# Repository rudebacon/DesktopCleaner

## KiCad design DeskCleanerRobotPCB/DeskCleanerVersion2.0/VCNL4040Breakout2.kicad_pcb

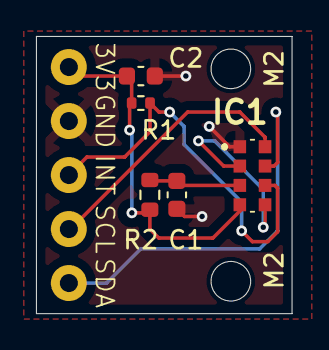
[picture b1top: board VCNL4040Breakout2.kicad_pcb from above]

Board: 2 copper layers, 14.2 x 15.4 mm, 12 parts (0 on the bottom side), 7 nets.

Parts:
3V3: +3.3V; Soldering_Holes_1mmH_2mmPad
C1: 0.1uF; C_0603_1608Metric
C2: 2.2uF; C_0603_1608Metric
GND: GND; Soldering_Holes_1mmH_2mmPad
IC1: VCNL4040M3OE
INT: INT1; Soldering_Holes_1mmH_2mmPad
M2, M2#2: MountingHole_2.2mm_M2
R1: 8.2k; R_0402_1005Metric
R2: 22; R_0603_1608Metric
SCL: SCL; Soldering_Holes_1mmH_2mmPad
SDA: SDA; Soldering_Holes_1mmH_2mmPad

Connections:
GND: C1.2, C2.2, GND.1, IC1.1 (GND)
unnamed: 3V3.1, C2.1, IC1.4 (A), R1.1, R2.2
unnamed: IC1.6 (INT), INT.1, R1.2
unnamed: IC1.2 (K(SENSOR)), IC1.5 (K(LED))
unnamed: IC1.8 (SCLK), SCL.1
unnamed: IC1.7 (SDAT), SDA.1
unnamed: C1.1, IC1.3 (VDD), R2.1

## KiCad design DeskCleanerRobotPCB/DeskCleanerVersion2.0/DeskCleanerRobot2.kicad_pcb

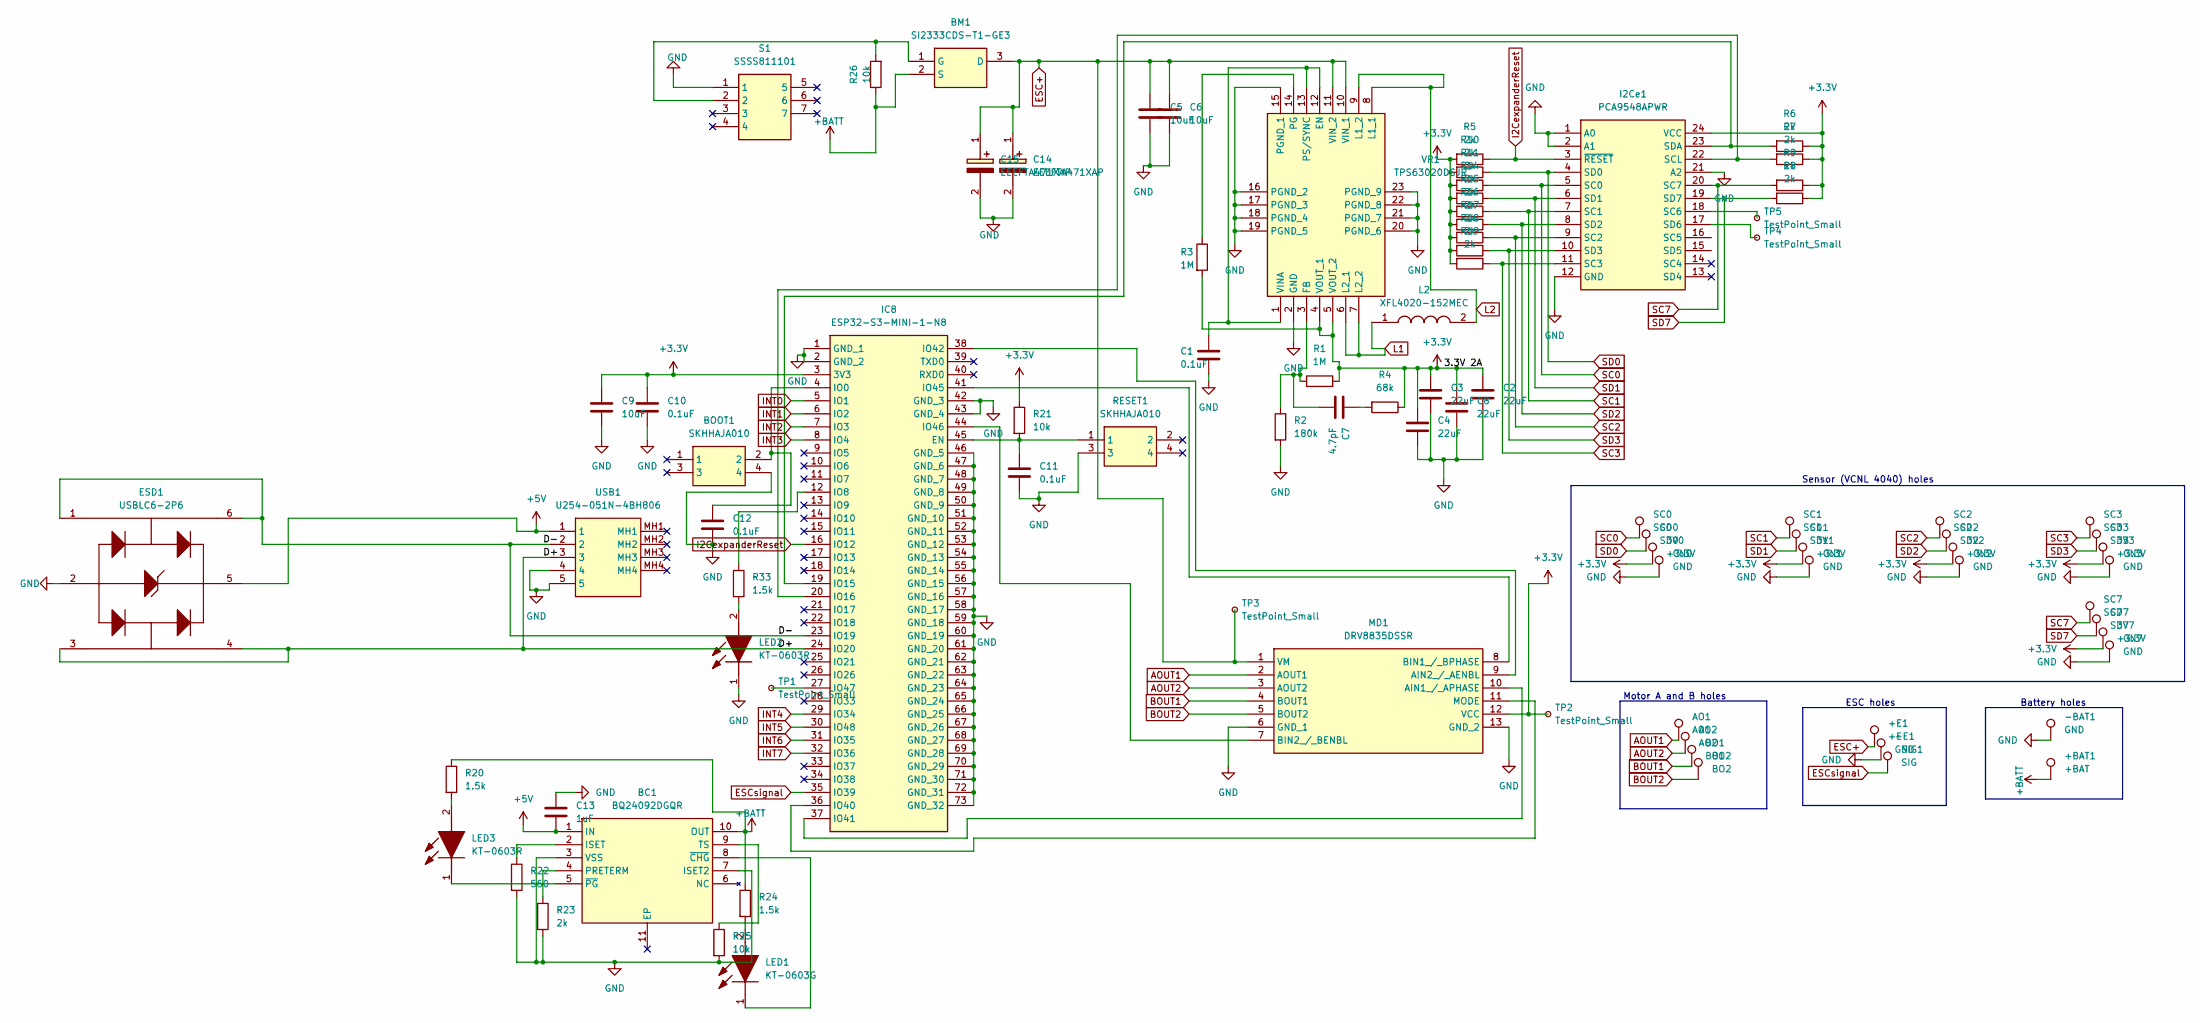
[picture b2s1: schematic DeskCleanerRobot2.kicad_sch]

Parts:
3V0, 3V1, 3V2, 3V3, 3V7: +3.3V; Soldering_Holes_1mmH_2mmPad
+BAT1: +BAT; Soldering_Holes_1mmH_2mmPad
+E1: +E; Soldering_Holes_1mmH_2mmPad
-BAT1: GND; Soldering_Holes_1mmH_2mmPad
-E1: GND; Soldering_Holes_1mmH_2mmPad
AO1: AO1; Soldering_Holes_1mmH_2mmPad
AO2: AO2; Soldering_Holes_1mmH_2mmPad
BC1: BQ24092DGQR; SOP50P490X110-11N; Manufacturer_Part_Number BQ24092DGQR; Mouser Part Number 595-BQ24092DGQR
BM1: SI2333CDS-T1-GE3; SOT95P237X112-3N; Manufacturer_Part_Number SI2333CDS-T1-GE3
BO1: BO1; Soldering_Holes_1mmH_2mmPad
BO2: BO2; Soldering_Holes_1mmH_2mmPad
BOOT1: SKHHAJA010; SKHHALA010; Manufacturer_Part_Number SKHHAJA010; Mouser Part Number 688-SKHHAJ
C1, C10, C11, C12: 0.1uF; C_0603_1608Metric
C2, C3, C4, C8: 22uF; C_0603_1608Metric
C5, C6, C9: 10uF; C_0603_1608Metric
C7: 4.7pF; C_0603_1608Metric
C13: 1uF; C_0603_1608Metric
C14, C15: EEEFTA471XAP; EEE0JA331XP; Manufacturer_Part_Number EEEFTA471XAP
ESD1: USBLC6-2P6; USBLC62P6; Manufacturer_Part_Number USBLC6-2P6; Mouser Part Number 511-USBLC6-2P6
GN0, GN1, GN2, GN3, GN7: GND; Soldering_Holes_1mmH_2mmPad
I2Ce1: PCA9548APWR; SOP65P640X120-24N; Manufacturer_Part_Number PCA9548APWR; Mouser Part Number 595-PCA9548APWR
IC8: ESP32-S3-MINI-1-N8; ESP32S3MINI1N8; Manufacturer_Part_Number ESP32-S3-MINI-1-N8; Mouser Part Number 356-ESP32-S3-MINI1N8
L2: XFL4020-152MEC; XFL4020152MEC; Manufacturer_Part_Number XFL4020-152MEC; Mouser Part Number 994-XFL4020-152MEC
LED1: KT-0603G; LEDC1608X70N; Manufacturer_Part_Number KT-0603R
LED2, LED3: KT-0603R; LEDC1608X70N; Manufacturer_Part_Number KT-0603R
MD1: DRV8835DSSR; Manufacturer_Part_Number DRV8835DSSR; Mouser Part Number 595-DRV8835DSSR
R1, R3: 1M; R_0603_1608Metric
R2: 180k; R_0603_1608Metric
R4: 68k; R_0603_1608Metric
R5, R6, R7, R8, R9, R10, R11, R14, R15, R16, R17, R18, R19, R23: 2k; R_0402_1005Metric
R20, R24, R33: 1.5k; R_0402_1005Metric
R21, R25, R26: 10k; R_0402_1005Metric
R22: 560; R_0402_1005Metric
RESET1: SKHHAJA010; SKHHALA010; Manufacturer_Part_Number SKHHAJA010; Mouser Part Number 688-SKHHAJ
S1: SSSS811101; Manufacturer_Part_Number SSSS811101; Mouser Part Number 688-SSSS811101
SC0: SC0; Soldering_Holes_1mmH_2mmPad
SC1: SC1; Soldering_Holes_1mmH_2mmPad
SC2: SC2; Soldering_Holes_1mmH_2mmPad
SC3: SC3; Soldering_Holes_1mmH_2mmPad
SC7: SC7; Soldering_Holes_1mmH_2mmPad
SD0: SD0; Soldering_Holes_1mmH_2mmPad
SD1: SD1; Soldering_Holes_1mmH_2mmPad
SD2: SD2; Soldering_Holes_1mmH_2mmPad
SD3: SD3; Soldering_Holes_1mmH_2mmPad
SD7: SD7; Soldering_Holes_1mmH_2mmPad
SIG1: SIG; Soldering_Holes_1mmH_2mmPad
TP1, TP2, TP3, TP4, TP5: TestPoint_Small; TestPoint_Pad_1.0x1.0mm
USB1: U254-051N-4BH806; U254051N4BH806; Manufacturer_Part_Number U254-051N-4BH806
VR1: TPS63020DSJR; Manufacturer_Part_Number TPS63020DSJR; Mouser Part Number 595-TPS63020DSJR

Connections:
+3.3V: 3V0.1, 3V1.1, 3V2.1, 3V3.1, 3V7.1, C2.1, C3.1, C4.1, C8.1, C9.1, C10.1, I2Ce1.24 (VCC), IC8.3 (3V3), MD1.12 (VCC), R1.2, R3.2, R4.1, R5.2, R6.1, R7.1, R8.1, R9.1, R10.2, R11.2, R14.2, R15.2, R16.2, R17.2, R18.2, R19.2, R21.1, TP2.1, VR1.4 (VOUT_1), VR1.5 (VOUT_2)
+5V: BC1.1 (IN), C13.2, ESD1.5 (VBUS), USB1.1
+BATT: +BAT1.1, BC1.10 (OUT), BM1.2 (S), R20.1, R24.1, R26.1
/D+: ESD1.3 (I/O2_1), ESD1.4 (I/O2_2), IC8.24 (IO20), USB1.3
/D-: ESD1.1 (I/O1_1), ESD1.6 (I/O1_2), IC8.23 (IO19), USB1.2
AOUT1: AO1.1, MD1.2 (AOUT1)
AOUT2: AO2.1, MD1.3 (AOUT2)
BOUT1: BO1.1, MD1.4 (BOUT1)
BOUT2: BO2.1, MD1.5 (BOUT2)
ESC+: +E1.1, BM1.3 (D), C5.1, C6.1, C14.1 (+), C15.1 (+), MD1.1 (VM), TP3.1, VR1.10 (VIN_1), VR1.11 (VIN_2)
ESCsignal: IC8.35 (IO39), SIG1.1
GND: -BAT1.1, -E1.1, BC1.3 (VSS), BC1.7 (ISET2), BOOT1.4, C1.2, C2.2, C3.2, C4.2, C5.2, C6.2, C8.2, C9.2, C10.2, C11.2, C12.2, C13.1, C14.2 (-), C15.2 (-), ESD1.2 (GND), GN0.1, GN1.1, GN2.1, GN3.1, GN7.1, I2Ce1.1 (A0), I2Ce1.2 (A1), I2Ce1.12 (GND), I2Ce1.21 (A2), IC8.1 (GND_1), IC8.2 (GND_2), IC8.42 (GND_3), IC8.43 (GND_4), IC8.46 (GND_5), IC8.47 (GND_6), IC8.48 (GND_7), IC8.49 (GND_8), IC8.50 (GND_9), IC8.51 (GND_10), IC8.52 (GND_11), IC8.53 (GND_12), IC8.54 (GND_13), IC8.55 (GND_14), IC8.56 (GND_15), IC8.57 (GND_16), IC8.58 (GND_17), IC8.59 (GND_18), IC8.60 (GND_19), IC8.61 (GND_20), IC8.62 (GND_21), IC8.63 (GND_22), IC8.64 (GND_23), IC8.65 (GND_24), IC8.66 (GND_25), IC8.67 (GND_26), IC8.68 (GND_27), IC8.69 (GND_28), IC8.70 (GND_29), IC8.71 (GND_30), IC8.72 (GND_31), IC8.73 (GND_32), LED2.1 (K), MD1.6 (GND_1), MD1.13 (GND_2), R2.2, R22.2, R23.2, R25.2, RESET1.3, S1.1, USB1.4, USB1.5, VR1.2 (GND), VR1.15 (PGND_1), VR1.16 (PGND_2), VR1.17 (PGND_3), VR1.18 (PGND_4), VR1.19 (PGND_5), VR1.20 (PGND_6), VR1.21 (PGND_7), VR1.22 (PGND_8), VR1.23 (PGND_9)
I2CexpanderReset: I2Ce1.3 (~RESET), IC8.16 (IO12), R5.1
INT0: IC8.5 (IO1)
INT1: IC8.6 (IO2)
INT2: IC8.7 (IO3)
INT3: IC8.8 (IO4)
INT4: IC8.29 (IO34)
INT5: IC8.30 (IO48)
INT6: IC8.31 (IO35)
INT7: IC8.32 (IO36)
L1: L2.1, VR1.6 (L2_1), VR1.7 (L2_2)
L2: L2.2, VR1.8 (L1_1), VR1.9 (L1_2)
unnamed: BC1.2 (ISET), R22.1
unnamed: BC1.4 (PRETERM), R23.1
unnamed: BC1.9 (TS), R25.1
unnamed: BC1.8 (~CHG), LED1.1 (K)
unnamed: BC1.5 (~PG), LED3.1 (K)
unnamed: BM1.1 (G), R26.2, S1.2
unnamed: C7.1, R4.2
unnamed: I2Ce1.18 (SC6), TP5.1
unnamed: I2Ce1.22 (SCL), IC8.20 (IO16), R7.2
unnamed: I2Ce1.17 (SD6), TP4.1
unnamed: I2Ce1.23 (SDA), IC8.19 (IO15), R6.2
unnamed: C11.1, IC8.45 (EN), R21.2, RESET1.1
unnamed: BOOT1.2, C12.1, IC8.4 (IO0)
unnamed: IC8.12 (IO8), R33.1
unnamed: IC8.36 (IO40), MD1.11 (MODE)
unnamed: IC8.37 (IO41), MD1.10 (AIN1_/_APHASE)
unnamed: IC8.38 (IO42), MD1.9 (AIN2_/_AENBL)
unnamed: IC8.41 (IO45), MD1.8 (BIN1_/_BPHASE)
unnamed: IC8.44 (IO46), MD1.7 (BIN2_/_BENBL)
unnamed: IC8.27 (IO47), TP1.1
unnamed: LED1.2 (A), R24.2
unnamed: LED2.2 (A), R33.2
unnamed: LED3.2 (A), R20.2
unnamed: C1.1, VR1.1 (VINA), VR1.12 (EN), VR1.13 (PS/SYNC)
unnamed: C7.2, R1.1, R2.1, VR1.3 (FB)
unnamed: R3.1, VR1.14 (PG)
SC0: I2Ce1.5 (SC0), R11.1, SC0.1
SC1: I2Ce1.7 (SC1), R15.1, SC1.1
SC2: I2Ce1.9 (SC2), R17.1, SC2.1
SC3: I2Ce1.11 (SC3), R19.1, SC3.1
SC7: I2Ce1.20 (SC7), R9.2, SC7.1
SD0: I2Ce1.4 (SD0), R10.1, SD0.1
SD1: I2Ce1.6 (SD1), R14.1, SD1.1
SD2: I2Ce1.8 (SD2), R16.1, SD2.1
SD3: I2Ce1.10 (SD3), R18.1, SD3.1
SD7: I2Ce1.19 (SD7), R8.2, SD7.1

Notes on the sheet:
Sensor (VCNL 4040) holes
ESC holes
Battery holes
Motor A and B holes

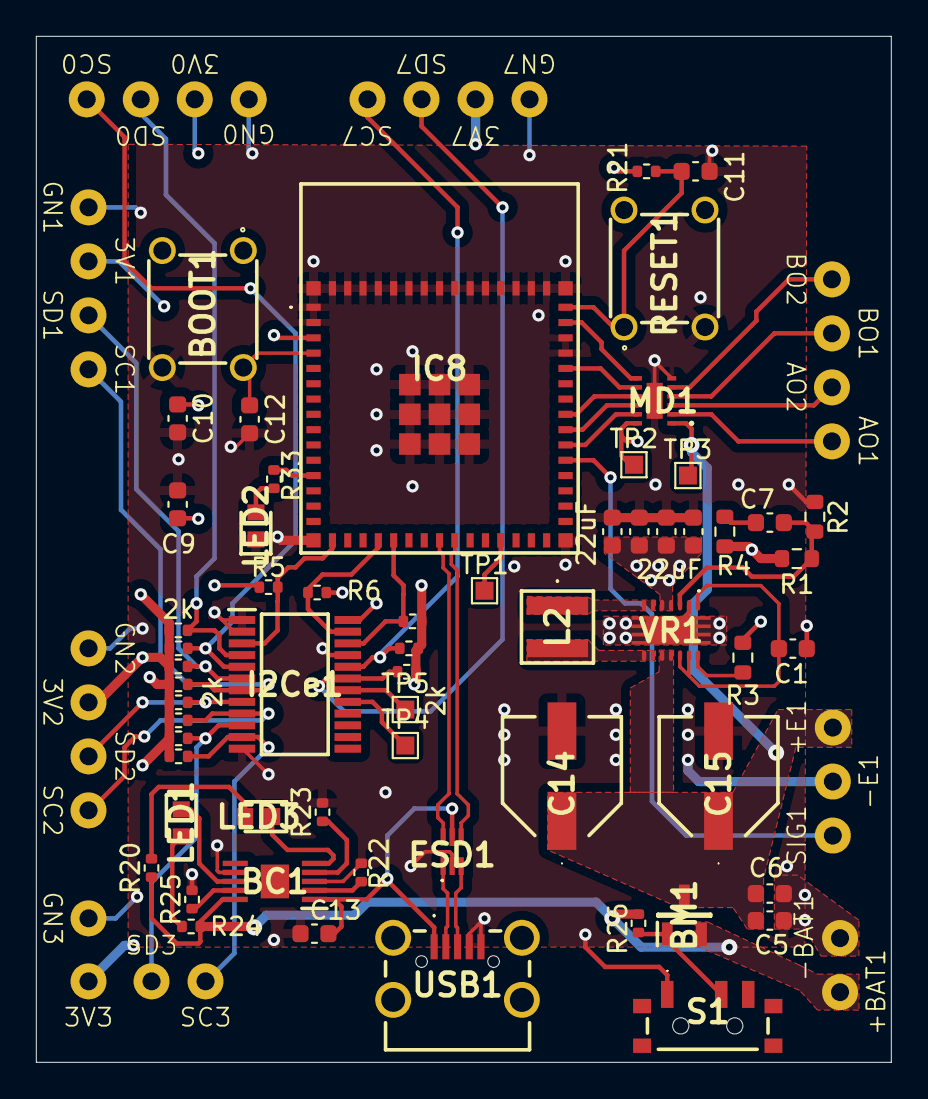
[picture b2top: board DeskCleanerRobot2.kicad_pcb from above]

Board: 4 copper layers, 47.5 x 57.0 mm, 89 parts (0 on the bottom side), 51 nets.

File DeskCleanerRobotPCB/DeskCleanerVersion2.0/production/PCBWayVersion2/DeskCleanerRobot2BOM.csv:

#,Reference,Qty,Manufacturer_Name,Manufacturer_Part_Number,Value,Description,Footprint,Type
1,BC1,1,Texas Instruments,BQ24092DGQR,BQ24092DGQR,"1A, Single-Input, Single-Cell Li-Ion Battery Charger with Operation Over JEITA and 10k NTC",SOP50P490X110-11N,SMD
2,BM1,1,Vishay,SI2333CDS-T1-GE3,SI2333CDS-T1-GE3,"SI2333CDS-T1-GE3, P-channel MOSFET Transistor 5.1 A 12 V, 3-Pin SOT-23",SOT95P237X112-3N,SMD
3,"BOOT1,RESET1",2,ALPS Electric,SKHHAJA010,SKHHAJA010,"Tact switch,PCB,SPST,black,0.98N o/force Black Stem Tactile Switch, SPST-NO 50 mA 4.3mm",SKHHALA010,thru-hole
4,C7,1,,,4.7pF,Unpolarized capacitor,Capacitor_SMD:C_0603_1608Metric,SMD
5,C13,1,,,1uF,Unpolarized capacitor,Capacitor_SMD:C_0603_1608Metric,SMD
6,"C1,C10,C11,C12",4,,,0.1uF,Unpolarized capacitor,Capacitor_SMD:C_0603_1608Metric,SMD
7,"C14,C15",2,Panasonic,EEEFTA471XAP,EEEFTA471XAP,FT SMT Al Elec Capacitor 470uF 10V Panasonic Aluminium Electrolytic Capacitor 470uF 10 V dc 6.3mm Surface Mount D8 series FT SMD lifetime 2000h,EEE0JA331XP,SMD
8,"C2,C3,C4,C8",4,,,22uF,Unpolarized capacitor,Capacitor_SMD:C_0603_1608Metric,SMD
9,"C5,C6,C9",3,,,10uF,Unpolarized capacitor,Capacitor_SMD:C_0603_1608Metric,SMD
10,ESD1,1,STMicroelectronics,USBLC6-2P6,USBLC6-2P6,ESD Suppressors / TVS Diodes High Speed Interface Protection Low Cap,USBLC62P6,SMD
11,I2Ce1,1,Texas Instruments,PCA9548APWR,PCA9548APWR,8-CHANNEL I2C SWITCH  WITH RESET,SOP65P640X120-24N,SMD
12,IC8,1,Espressif Systems,ESP32-S3-MINI-1-N8,ESP32-S3-MINI-1-N8,"WiFi Development Tools - 802.11 [Engineering Samples] SMD Module, ESP32-S3FN8, 8 MB SPI Flash, PCB Antenna",ESP32S3MINI1N8,SMD
13,L2,1,COILCRAFT,XFL4020-152MEC,XFL4020-152MEC,"COILCRAFT - XFL4020-152MEC - Power Inductor (SMD), 1.5 H, 9.1 A, Shielded, 4.1 A, XFL4020",XFL4020152MEC,SMD
14,LED1,1,Hubei KENTO Elec,KT-0603G,KT-0603G,Green 0603 Light Emitting Diodes (LED) ,LEDC1608X70N,SMD
15,"LED2,LED3",2,Hubei KENTO Elec,KT-0603R,KT-0603R,Red 0603 Light Emitting Diodes (LED) ,LEDC1608X70N,SMD
16,MD1,1,Texas Instruments,DRV8835DSSR,DRV8835DSSR,Motor / Motion / Ignition Controllers & Drivers 1.5A Low Vlt Stepper Motor,DRV8835DSSR,SMD
17,R2,1,,,180k,Resistor,Resistor_SMD:R_0603_1608Metric,SMD
18,R4,1,,,68k,Resistor,Resistor_SMD:R_0603_1608Metric,SMD
19,R22,1,,,560,Resistor,Resistor_SMD:R_0402_1005Metric,SMD
20,"R1,R3",2,,,1M,Resistor,Resistor_SMD:R_0603_1608Metric,SMD
21,"R20,R24,R33",3,,,1.5k,Resistor,Resistor_SMD:R_0402_1005Metric,SMD
22,"R21,R25,R26",3,,,10k,Resistor,Resistor_SMD:R_0402_1005Metric,SMD
23,"R5,R6,R7,R8,R9,R10,R11,R14,R15,R16,R17,R18,R19,R23",14,,,2k,Resistor,Resistor_SMD:R_0402_1005Metric,SMD
24,S1,1,ALPS Electric,SSSS811101,SSSS811101,Slide Switches SPDT HORZ GRND 1.5mm,SSSS811101,SMD
25,USB1,1,XKB Connectivity,U254-051N-4BH806,U254-051N-4BH806,USB Connectors SMD RoHS,U254051N4BH806,thru-hole
26,VR1,1,Texas Instruments,TPS63020DSJR,TPS63020DSJR,Conv DC-DC 1.8V to 5.5V Synchronous Step Down/Synchronous Step Up Single-Out 1.2V to 5.5V 3A 14-Pin VSON EP T/R,TPS63020DSJR,SMD

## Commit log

2024-12-19 Create DeskCleanerRobotPCB.ino
    Two sensors working but connection is finnicky so sometimes have to reset to get sensor 1/channel 0 "unstuck"
2025-05-25 moved other files in
